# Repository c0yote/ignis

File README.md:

# ignis

ignis is a graph controllable electric oven, control board, and software interface for foundry work, heat treating steel, and reflow soldering printed circuit boards.

The project is completely open source and open hardware.  All hardware design artifacts are licensed under a Creative Commons license and all software and firmware under the MIT License.

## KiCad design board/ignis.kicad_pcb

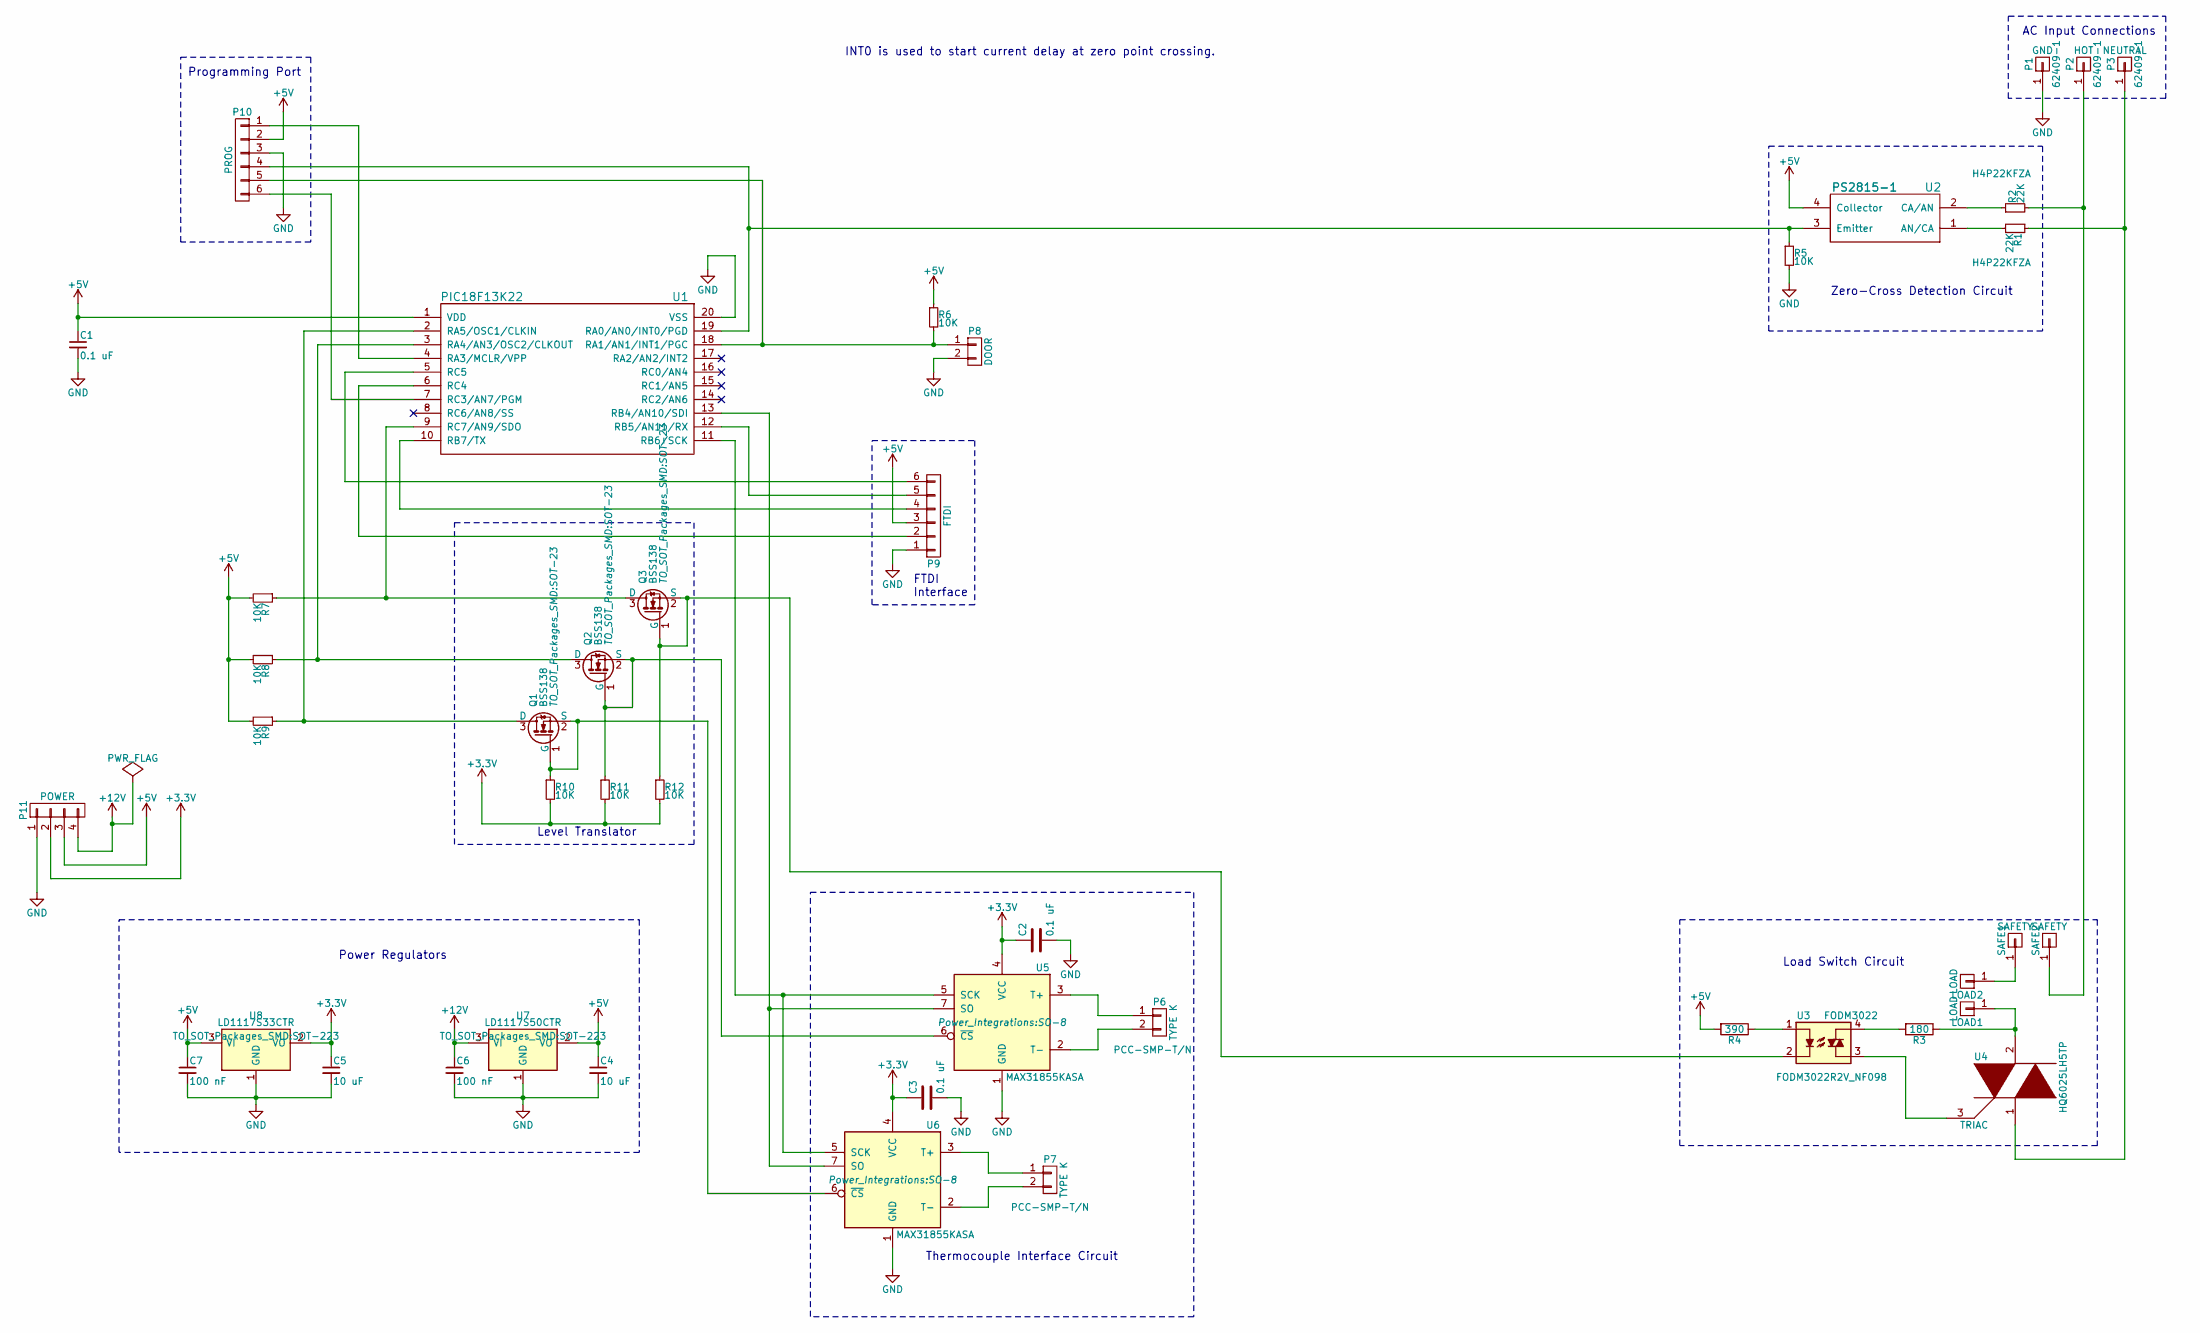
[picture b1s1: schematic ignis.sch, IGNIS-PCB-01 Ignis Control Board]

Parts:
C1, C2, C3: 0.1 uF; C_0603
C4, C5: 10 uF; C_0603
C6, C7: 100 nF; C_0603
LOAD1, LOAD2: LOAD; 62409-1
P1: GND; 62409-1
P2: HOT; 62409-1
P3: NEUTRAL; 62409-1
P6, P7: TYPE K; PCC-SMP-TN
P8: DOOR; TerminalBlock_Pheonix_MPT-2.54mm_2pol
P9: FTDI; PINHEAD1-6
P10: PROG; Pin_Header_Straight_1x06
P11: POWER; TerminalBlock_Pheonix_MPT-2.54mm_4pol
Q1, Q2, Q3: BSS138; SOT-23
R1, R2: 22K; R_0603
R3: 180; R_0603
R4: 390; R_0603
R5, R6, R7, R8, R9, R10, R11, R12: 10K; R_0603
SAFE1, SAFE2: SAFETY; 62409-1
U1: PIC18F13K22; SSOP-20
U2: PS2815-1
U3: FODM3022; FODM30XX
U4: TRIAC; TO-220_Neutral123_Horizontal_LargePads
U5, U6: MAX31855KASA; SO-8
U7: LD1117S50CTR; SOT-223
U8: LD1117S33CTR; SOT-223

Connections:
+3V3: C2.1, C3.1, C5.1, P11.2, R10.2, R11.2, R12.2, U5.4 (VCC), U6.4 (VCC), U8.2 (VO)
+5V: C1.1, C4.1, C7.1, P9.3, P10.2, P11.3, R4.2, R6.1, R7.2, R8.2, R9.2, U1.1 (VDD), U2.4 (Collector), U7.2 (VO), U8.3 (VI)
+12V: C6.1, P11.4, U7.3 (VI)
GND: C1.2, C2.2, C3.2, C4.2, C5.2, C6.2, C7.2, P1.1, P8.2, P9.1, P10.3, P11.1, R5.2, U1.20 (VSS), U5.1 (GND), U6.1 (GND), U7.1 (GND), U8.1 (GND)
unnamed: LOAD1.1, R3.1, U4.2
unnamed: LOAD2.1, SAFE1.1
unnamed: P2.1, R2.2, SAFE2.1
unnamed: P3.1, R1.1, U4.1
unnamed: P6.1, U5.3 (T+)
unnamed: P6.2, U5.2 (T-)
unnamed: P7.1, U6.3 (T+)
unnamed: P7.2, U6.2 (T-)
unnamed: P9.2, U1.6 (RC4)
unnamed: P9.4, U1.10 (RB7/TX)
unnamed: P9.5, U1.12 (RB5/AN11/RX)
unnamed: P9.6, U1.5 (RC5)
unnamed: P10.1, U1.4 (RA3/MCLR/VPP)
unnamed: P10.4, R5.1, U1.19 (RA0/AN0/INT0/PGD), U2.3 (Emitter)
unnamed: P8.1, P10.5, R6.2, U1.18 (RA1/AN1/INT1/PGC)
unnamed: P10.6, U1.7 (RC3/AN7/PGM)
unnamed: Q1.1 (G), Q1.2 (S), R10.1, U6.6 (~CS~)
unnamed: Q1.3 (D), R9.1, U1.2 (RA5/OSC1/CLKIN)
unnamed: Q2.1 (G), Q2.2 (S), R11.1, U5.6 (~CS~)
unnamed: Q2.3 (D), R8.1, U1.3 (RA4/AN3/OSC2/CLKOUT)
unnamed: Q3.1 (G), Q3.2 (S), R12.1, U3.2
unnamed: Q3.3 (D), R7.1, U1.9 (RC7/AN9/SDO)
unnamed: R1.2, U2.1 (AN/CA)
unnamed: R2.1, U2.2 (CA/AN)
unnamed: R3.2, U3.4
unnamed: R4.1, U3.1
unnamed: U1.11 (RB6/SCK), U5.5 (SCK), U6.5 (SCK)
unnamed: U1.13 (RB4/AN10/SDI), U5.7 (SO), U6.7 (SO)
unnamed: U3.3, U4.3

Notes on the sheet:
INT0 is used to start current delay at zero point crossing.
AC Input Connections
Thermocouple Interface Circuit
Load Switch Circuit
Zero-Cross Detection Circuit
Programming Port
FTDI Interface
Level Translator
Power Regulators

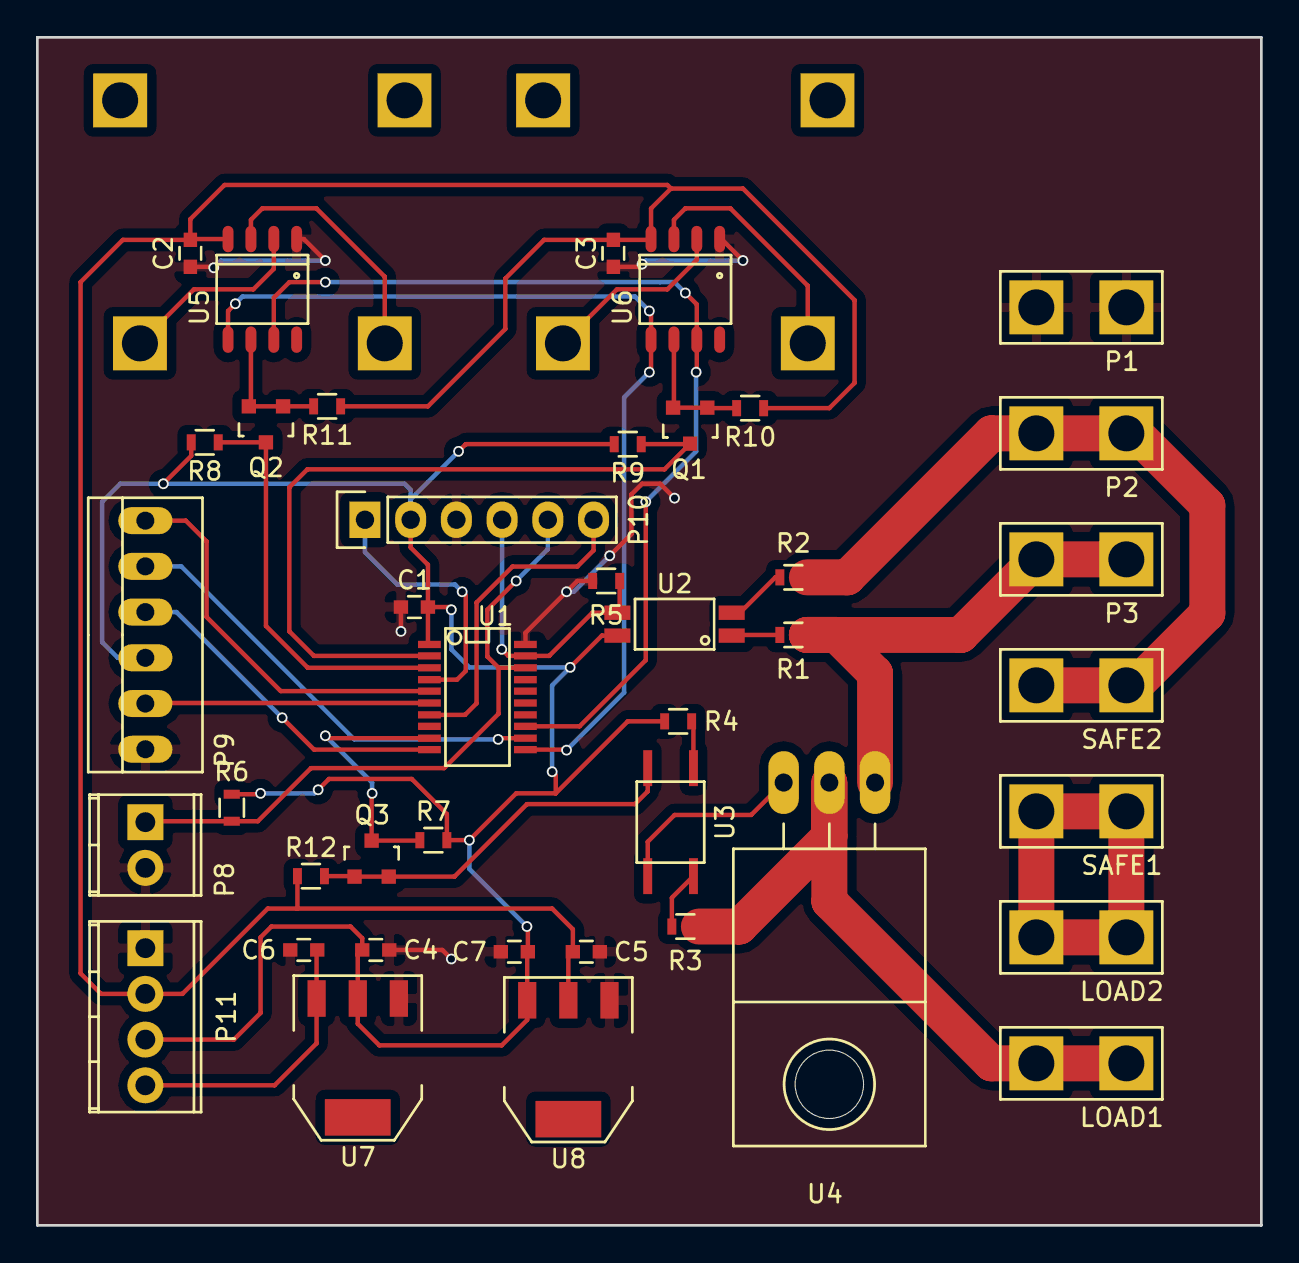
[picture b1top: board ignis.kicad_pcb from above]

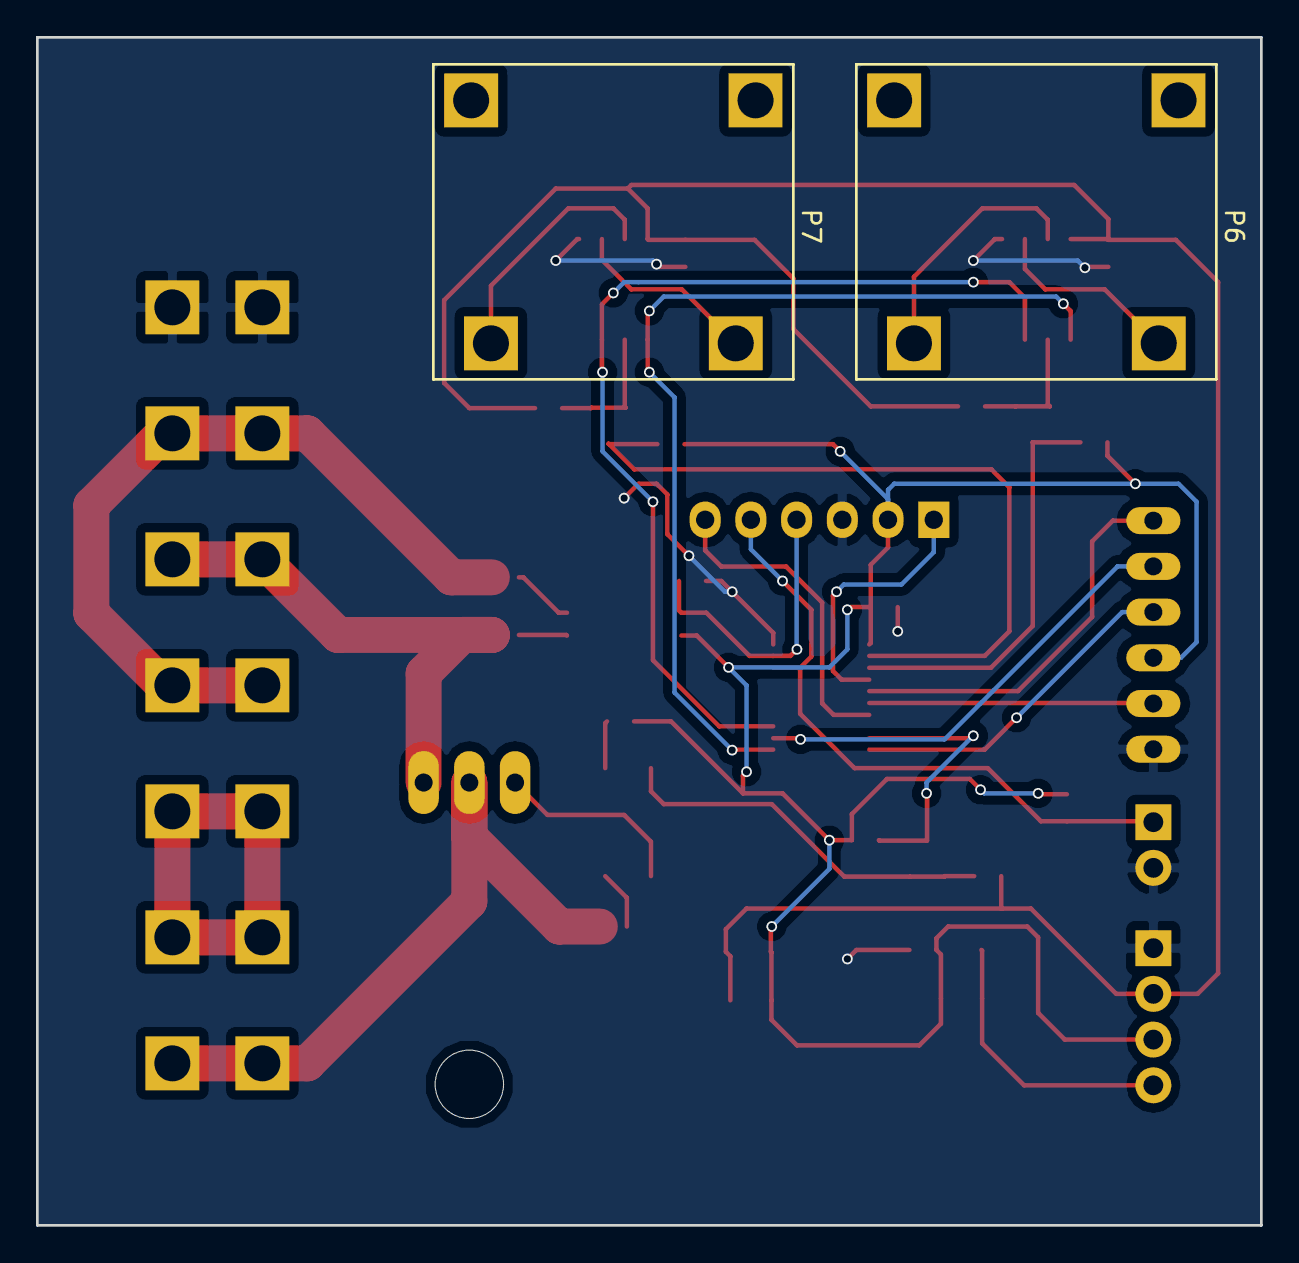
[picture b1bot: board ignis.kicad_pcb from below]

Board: 2 copper layers, 68.0 x 66.0 mm, 43 parts (2 on the bottom side), 33 nets.

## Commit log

2016-07-18 Initial commit.
2016-07-24 Revised insulation plan.
2016-09-03 Finalized the Zero-Cross circuit via experimentation.
2016-09-03 TRIAC control circuit.
2016-09-03 Control software project skeleton.
2016-09-03 Draft of a body frame CADs.
2016-09-03 License and Readme.
2016-09-03 Formatting.
2017-02-17 Layout done for Rev. 0 bench test board.
2017-02-24 Edge fix and plot for prototype.

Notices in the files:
board/ignis.sch:
https://creativecommons.org/licenses/by-sa/4.0
Creative Commons Attribution-ShareAlike 4.0 International
Copyright 2016 U.G. Wilson
